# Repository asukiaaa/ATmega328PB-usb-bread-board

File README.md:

# ATmega328PB-usb-bread-board

## Components

- [5V 2A Diode](https://akizukidenshi.com/catalog/g/gI-02073/)
- [4.7f 0402](https://akizukidenshi.com/catalog/g/gP-07504/)
- 0.1f 0402
- 4.7uf 0402
- [MEMS 16MHz](https://akizukidenshi.com/catalog/g/gI-11094/)
- [USB microB](https://www.digikey.jp/product-detail/ja/molex/1050170001/WM1399CT-ND/2350885)
- CP2102N
- Resistor 0603 47k, 22k, 10k and 1k
- LED 0603
- [TVS Diode array ESDR0502NMUTBG](https://www.digikey.jp/product-detail/ja/on-semiconductor/ESDR0502NMUTBG/ESDR0502NMUTBGOSCT-ND/3462275)

## License

MIT

## References

- [ATmega328PB datasheet (PDF)](http://ww1.microchip.com/downloads/en/DeviceDoc/40001906A.pdf)
- [MiniCore](https://github.com/MCUdude/MiniCore)
- [MiniCore/avr/variants/pb-variant/pins_arduino.h](https://github.com/MCUdude/MiniCore/blob/master/avr/variants/pb-variant/pins_arduino.h)
- [A-Star 328PB Micro schematic](https://www.pololu.com/file/0J1463/a-star-328pb-micro-schematic.pdf)
- [Grove system](https://wiki.seeedstudio.com/Grove_System/)
- [CP210x 5V Tolerance](https://www.silabs.com/community/interface/knowledge-base.entry.html/2004/02/18/cp210x_5v_tolerance-J582)
- [Devkitc v4 schema (PDF)](https://dl.espressif.com/dl/schematics/esp32_devkitc_v4-sch.pdf)

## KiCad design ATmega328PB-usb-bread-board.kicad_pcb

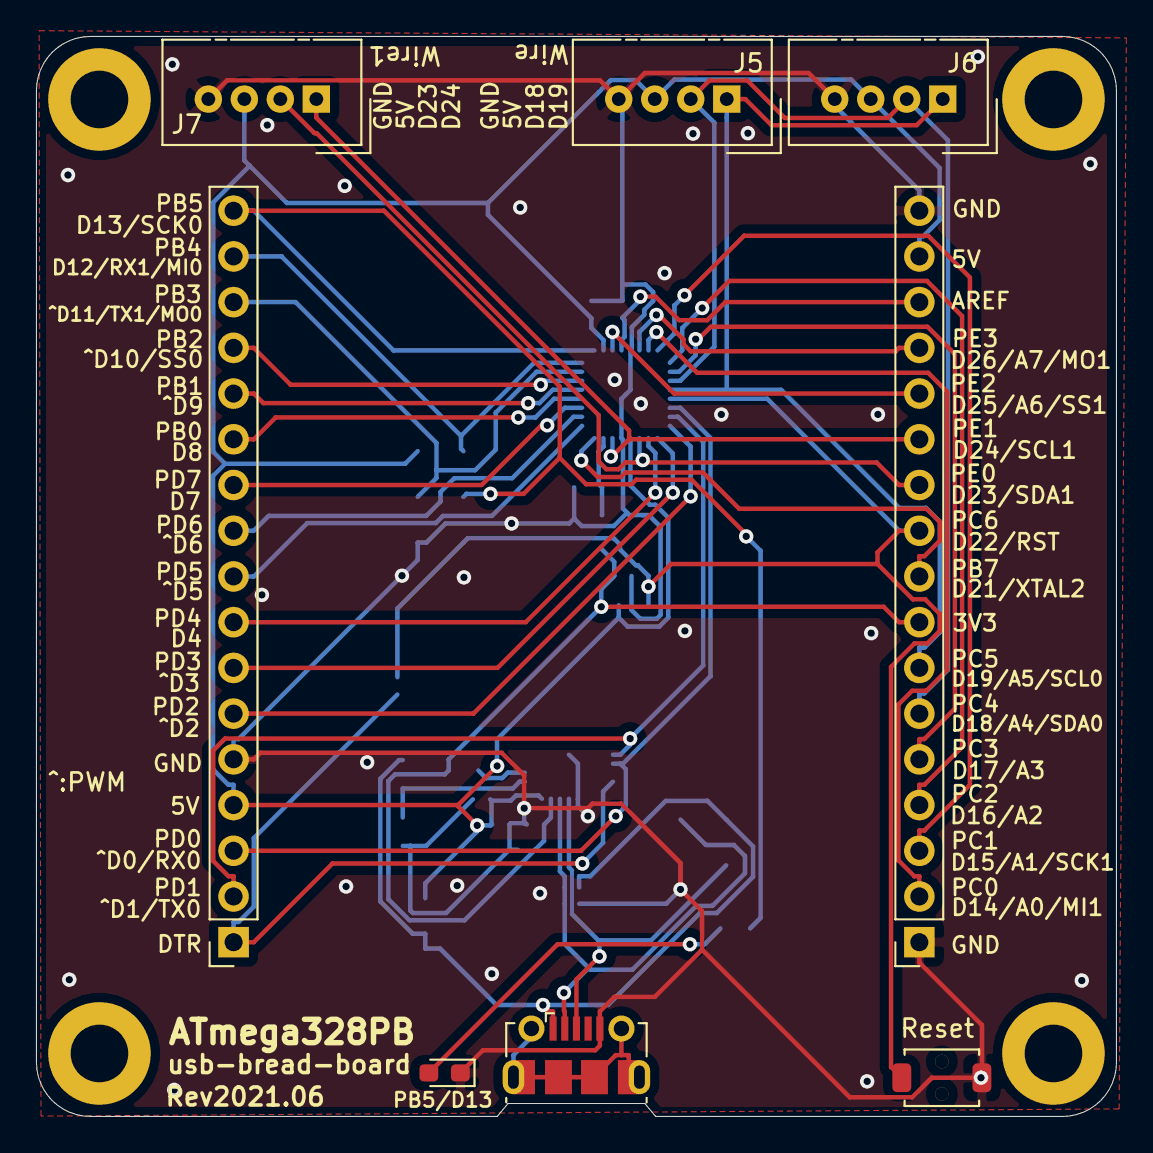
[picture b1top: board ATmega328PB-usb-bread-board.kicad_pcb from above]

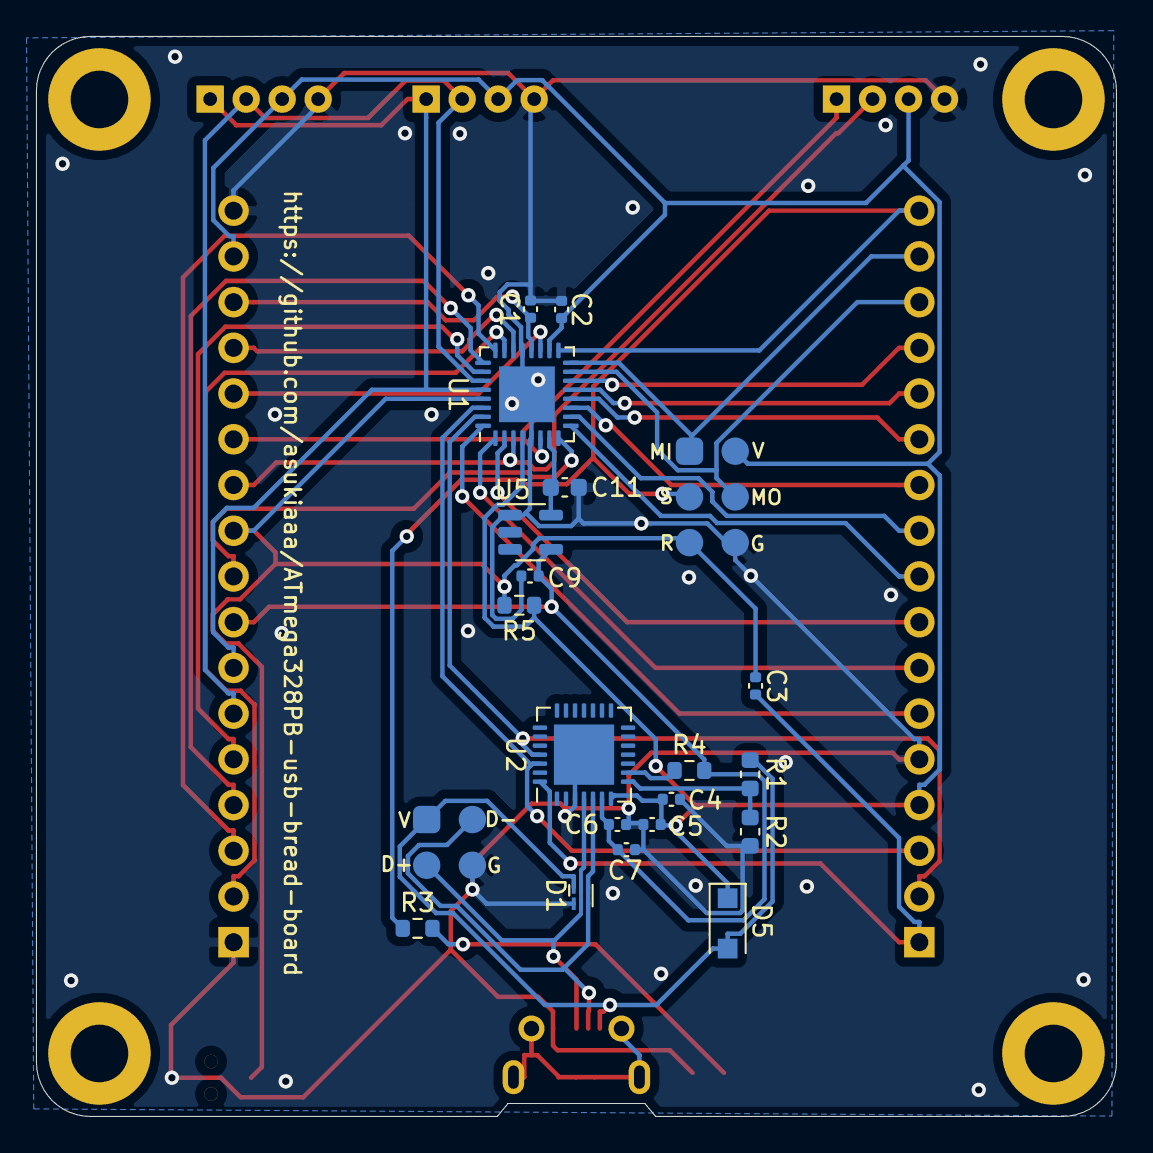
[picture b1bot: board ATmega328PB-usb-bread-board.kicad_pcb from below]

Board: 2 copper layers, 60.0 x 60.0 mm, 33 parts (21 on the bottom side), 38 nets.

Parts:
C1, C2, C3, C4, C7, C9: 0.1uf; C_0402_1005Metric
C5, C6: 4.7uf; C_0402_1005Metric
C11: 15pf; C_0603_1608Metric
D1: Diode_4array_ESDR0502NMUTBG; OnSemi_UDFN-6_1.2x1.0mm_P0.4mm
D4: PB5/D13; LED_0603_1608Metric_Pad1.05x0.95mm_HandSolder
D5: D; D_SOD-123F
J1, J2: Conn_01x17; PinSocket_1x17_P2.54mm_Vertical
J3: USB_B_Micro; USB_Micro-B_Molex-105017-0001
J4: AVR-ISP-6; 2x03_P2.54mm_ISP_Pads
J5, J6, J7: Grove-I2C-connector; NS-Tech_Grove_1x04_P2mm_Vertical
J8: USB_test; 2x02_P2.54mm_USB_Pads
R1: 22.1k; R_0603_1608Metric
R2: 47.5k; R_0603_1608Metric
R3: 22k; R_0603_1608Metric
R4: 1k; R_0603_1608Metric
R5: 10k; R_0603_1608Metric
REF1, REF2, REF3, REF4: MountingHole_3.2mm_M3_ISO7380_Pad
SW1: SW_Push; SW_Push_TVAF06
U1: ATmega328PB-MU; QFN-32-1EP_5x5mm_P0.5mm_EP3.1x3.1mm
U2: CP2102N-A01-GQFN28; QFN-28-1EP_5x5mm_P0.5mm_EP3.35x3.35mm
U5: SiT2001B-MEMS-Clock-Generator; SOT-23-5

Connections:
+3V3: C6.1, C7.1, C9.1, J2.8, R4.2, U2.6, U5.4
/16MHz: C11.1, U1.7, U5.5
/D+: D1.2, D1.5, J3.3, J8.3, U2.4
/D-: D1.3, D1.4, J3.2, J8.2, U2.5
/DTR: C3.2, J1.1, U2.28
/USB_UART_RX: J1.2, U1.31, U2.25
/USB_UART_TX: J1.3, U1.30, U2.26
/aref: C1.1, J2.15, U1.20
/pb0: J1.12, U1.12
/pb1: J1.13, U1.13
/pb2: J1.14, U1.14
/pb3: J1.15, J4.4, U1.15
/pb4: J1.16, J4.1, U1.16
/pb5: J1.17, J4.3, R3.1, U1.17
/pb7: J2.9, U1.8
/pc0: J2.2, U1.23
/pc1: J2.3, U1.24
/pc2: J2.4, U1.25
/pc3: J2.5, U1.26
/pc4: J2.6, J5.2, J6.2, U1.27
/pc5: J2.7, J5.1, J6.1, U1.28
/pc6: C3.1, J2.10, J4.5, R5.2, SW1.2, U1.29
/pd2: J1.6, U1.32
/pd3: J1.7, U1.1
/pd4: J1.8, U1.2
/pd5: J1.9, U1.9
/pd6: J1.10, U1.10
/pd7: J1.11, U1.11
/pe0: J2.11, J7.2, U1.3
/pe1: J2.12, J7.1, U1.6
/pe2: J2.13, U1.19
/pe3: J2.14, U1.22
GND: C1.2, C2.2, C4.2, C5.2, C6.2, C7.2, C9.2, C11.2, D1.1, D4.1, J1.5, J2.1, J2.17, J3.5, J4.6, J5.4, J6.4, J7.4, J8.4, R2.2, SW1.1, U1.5, U1.21, U1.33, U2.3, U2.29, U5.1
unnamed: D4.2, R3.2
unnamed: R1.2, R2.1, U2.8
unnamed: R4.1, U2.9
VBUS: D1.6, D5.2, J3.1, J8.1, R1.1
VCC: C2.1, C4.1, C5.1, D5.1, J1.4, J2.16, J4.2, J5.3, J6.3, J7.3, R5.1, U1.4, U1.18, U2.7

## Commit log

2020-10-18 Put 3V3 regulator and 16MHz MEMS to shematic
2020-10-20 Add pullup resister and condensors for cp2102n
2020-10-20 Supply 3V3 to cp2102
2020-10-20 Use cp2102 as 3v3 regulator
2020-10-20 Remove jumper for DTR
2020-10-20 Add CP2102 5V tolerance info to readme
2020-10-20 Change diode position on schema
2020-10-20 Remove jumper for AVCC
2020-10-20 Update pcb
2020-10-20 Add link of devkitc v4 to references on readme
2020-10-31 Update submodule commit
2020-11-03 Change zenar and change position of led and usb
2021-03-13 Use diode array and update holes position as Rev2021.03
2021-04-11 Correct pin asign for Wire1 grove connector
2021-04-12 Add pullup resistor to RST
2021-04-12 Add labels about pins for Grove connectors
2021-04-12 Rename VCC label to 5V
2021-04-12 Expand pad for diode array
2021-04-29 Remove amplifier
2021-04-29 Update footprint position of mems
2021-04-29 Update a list of components and update label for resistors
2021-05-10 Update fill
2021-05-10 Correct pin label for wire connector
2021-05-10 Add schema pdf
2021-05-17 Supply 3V3 for mems
2021-05-18 Add USB pads
2021-06-06 Add reset button
2021-06-06 Add link of switch to readme
2021-06-08 Fill again
2021-06-22 Change position of D13
